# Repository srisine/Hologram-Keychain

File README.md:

# Hologram-Keychain

A mini pocket hologram display that uses Beam Splitter Cube to project the contents of a 0.96inch OLED appearing as hologram.

<H1>Features:</H1>
1. Cool 3D build in holograms: Built in holograms that can rotate or move in 3D.
2. Connect from phone: Using ESP32's built in wifi and bluetooth capability, we can control the hologram using our phone's

<H1>Inspiration:</H1>

<H1>CAD:</H1>
Designed in Fusion 360:

<H1>PCB:</H1>
Designed in KiCad:

# BOM

| Component | Qty | Source | Price (USD) | Link |
| :--- | :---: | :---: | :---: | :---: |
| Seeed Studio XIAO ESP32-C3 | 1 | Online | $8.71 | [Robu.in](https://robu.in/product/seeed-studio-xiao-esp32c3-tiny-mcu-board-with-wi-fi-and-ble-battery-charge-supported-power-efficiency-and-rich-interface/) |
| 0.96-inch I2C OLED Display | 1 | Online | $3.50 | [Robu.in](https://robu.in/product/0-96-inch-i2c-iic-oled-lcd-module-4pin-with-vcc-gnd-white/) |
| Beam Splitter Cube (20x20x20mm) | 1 | Online | $35.99 | [Amazon](https://www.amazon.com/dp/B0B34FK2GF?lv=shuf&linkCode=ml1&linkId=20432106a03f15aeb801518b7a7205ca&gaOptInStatus=true&tag=rapsduinouno-20&channelId=1&ref_=cm_sw_r_as_gl_apa_gl_i_X6DF8AVB1PKCPZQ9A28V&plpRedirect=mhFallback&th=1) |
| Custom PCB Board | 1 | Online | $10.00 | [JLCPCB](https://jlcpcb.com) |
| 3D Printed Case | 1 set | Online | $2.00 | Robu.in |
| M3 Screws & Standoffs Assortment | 1 set | Local | ~$2.00 | Local Market |
| **Subtotal (Online Purchases)** | **5** | **Online** | **~$60.20** | **—** |
| **Subtotal (Local Purchases)** | **1** | **Local** | **~$2.00** | **—** |
| **Grand Total** | **6 items** | **All** | **~$62.20** | **—** |

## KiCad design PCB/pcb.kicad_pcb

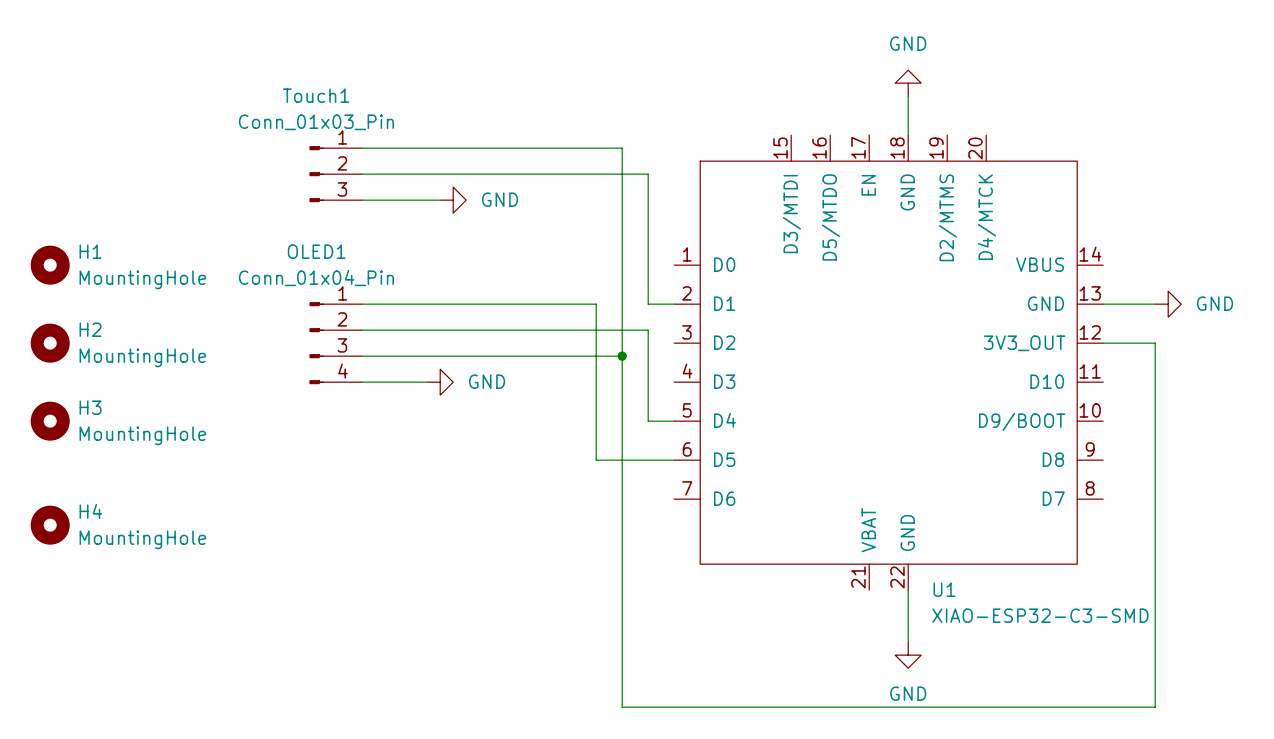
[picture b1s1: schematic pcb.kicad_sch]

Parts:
H1, H2, H3, H4: MountingHole; MountingHole_2.1mm
OLED1: Conn_01x04_Pin; PinHeader_1x04_P2.54mm_Vertical
Touch1: Conn_01x03_Pin; PinHeader_1x03_P2.54mm_Vertical
U1: XIAO-ESP32-C3-SMD

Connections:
GND: OLED1.4, Touch1.3, U1.13 (GND), U1.18 (GND), U1.22 (GND)
unnamed: OLED1.1, U1.6 (D5)
unnamed: OLED1.2, U1.5 (D4)
unnamed: OLED1.3, Touch1.1, U1.12 (3V3_OUT)
unnamed: Touch1.2, U1.2 (D1)

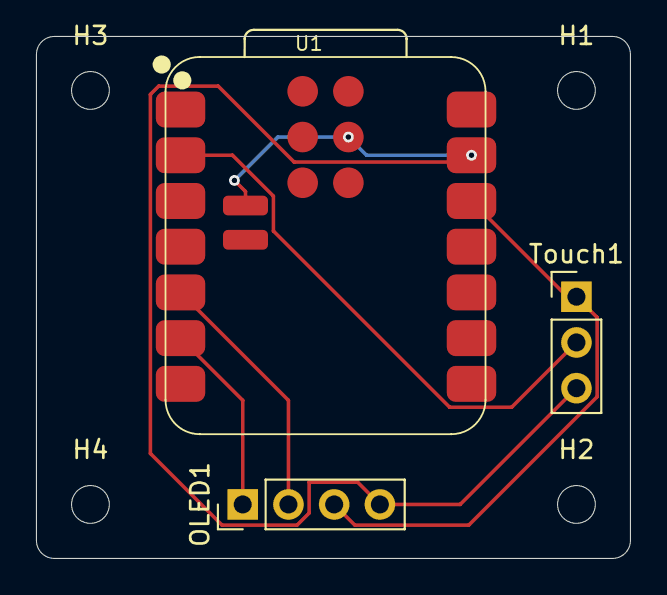
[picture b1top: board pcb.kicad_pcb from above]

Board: 2 copper layers, 33.0 x 29.0 mm, 7 parts (0 on the bottom side), 5 nets.
